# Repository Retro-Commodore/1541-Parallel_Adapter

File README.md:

# RCEU1505 - 1541-Parallel_Adapter
This is an adapter to easier add a parallel port for the Commodore 1541 and 1541-II diskette drive.
You can (and should) read more on Peter's site https://ist.uwaterloo.ca/~schepers/1541par.html

Item list.
* 15CM 10 wire flatcable.
  * or 8 wire flatcable for ZoomFloppy.
* 15pin D-sub female(not the VGA type connector), either solder or for IDC ribbon cable (last one recommended).
* 40 pins IC socket.
* 2 x 20 pins sil header male-male. (turned/tulip recommended).

All items can be found on eBay or your favorite electronics pusher.

**Let the PCB be as thin as possible, otherwise you need thicker washers. Testet is a 0.8mm thick adapter. **

Washers are needed for the 1541-II drive to lift the mechanical parts.
1.6mm (2 x 0.8mm) height with an inner diameter of 4mm is just sufficient to lift the drive.
It hasn't been physically testet on a 1541 drive, if you're intending to use this drive, let me know how it fits, so I can update this document.

Connecting the adapter to ZoomFloppy is described below, if you need to connect the drive to a C64, you should visit Peter's site for more help.

On 1541 shortboard the chip is UC3, and on the long board it's UAB1.

For solder pins

Adapter | 15pin D-sub female
------------ | -------------
Pin 1 | Pin 1
Pin 2 | Pin 2
Pin 3 | Pin 3
Pin 4 | Pin 4
Pin 5 | Pin 5
Pin 6 | Pin 6
Pin 7 | Pin 7
Pin 8 | Pin 8

Soldering the cable for this is just the same pinout

15pin D-sub male | 15pin D-sub female
------------ | -------------
Pin 1 | Pin 1
Pin 2 | Pin 2
Pin 3 | Pin 3
Pin 4 | Pin 4
Pin 5 | Pin 5
Pin 6 | Pin 6
Pin 7 | Pin 7
Pin 8 | Pin 8

If you choose to use the connector to press the IDC connector and don't want to use a 15 pin cable wasting 7 wires, you can hook it up like this.

Adapter | 15pin D-sub female (IDC)
------------ | -------------
Pin 1 | Pin 1
Pin 2 | Pin 9
Pin 3 | Pin 2
Pin 4 | Pin 10
Pin 5 | Pin 3
Pin 6 | Pin 11
Pin 7 | Pin 4
Pin 8 | Pin 12

The cable should be soldered accordingly

15pin D-sub female | 15pin D-sub male
------------ | -------------
Pin 1 | Pin 1
Pin 2 | Pin 9
Pin 3 | Pin 2
Pin 4 | Pin 10
Pin 5 | Pin 3
Pin 6 | Pin 11
Pin 7 | Pin 4
Pin 8 | Pin 12

Many thanks to [Peter Schepers](https://ist.uwaterloo.ca/~schepers/1541par.html).

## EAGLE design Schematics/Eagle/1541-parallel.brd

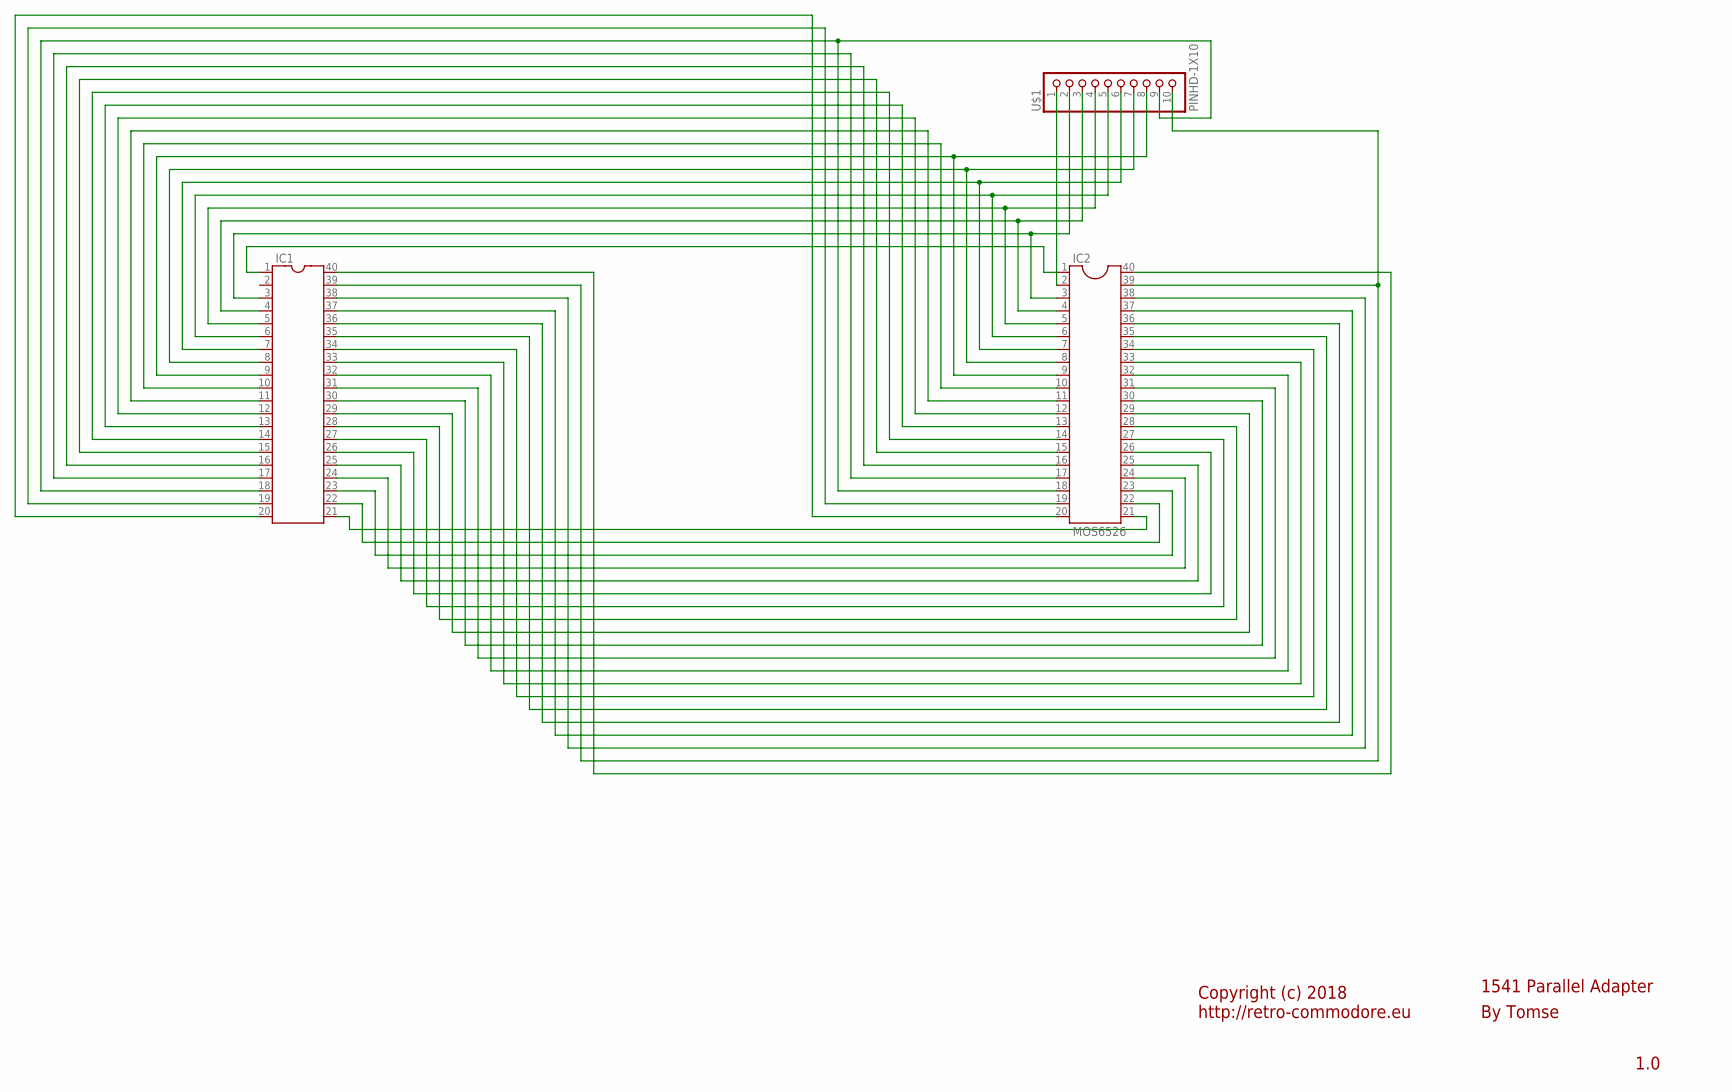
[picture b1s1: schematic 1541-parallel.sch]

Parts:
IC1: IC-PACKAGE_DIL40
IC2: MOS6526; DIL40
U$1: PINHD-1X10; 1X10-BIG

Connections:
unnamed: IC1.1, IC2.1
unnamed: IC1.3, IC2.3, U$1.2
unnamed: IC1.4, IC2.4, U$1.3
unnamed: IC1.5, IC2.5, U$1.4
unnamed: IC1.6, IC2.6, U$1.5
unnamed: IC1.7, IC2.7, U$1.6
unnamed: IC1.8, IC2.8, U$1.7
unnamed: IC1.9, IC2.9, U$1.8
unnamed: IC1.10, IC2.10
unnamed: IC1.11, IC2.11
unnamed: IC1.12, IC2.12
unnamed: IC1.13, IC2.13
unnamed: IC1.14, IC2.14
unnamed: IC1.15, IC2.15
unnamed: IC1.16, IC2.16
unnamed: IC1.17, IC2.17
unnamed: IC1.18, IC2.18, U$1.9
unnamed: IC1.19, IC2.19
unnamed: IC1.20, IC2.20
unnamed: IC1.21, IC2.21
unnamed: IC1.22, IC2.22
unnamed: IC1.23, IC2.23
unnamed: IC1.24, IC2.24
unnamed: IC1.25, IC2.25
unnamed: IC1.26, IC2.26
unnamed: IC1.27, IC2.27
unnamed: IC1.28, IC2.28
unnamed: IC1.29, IC2.29
unnamed: IC1.30, IC2.30
unnamed: IC1.31, IC2.31
unnamed: IC1.32, IC2.32
unnamed: IC1.33, IC2.33
unnamed: IC1.34, IC2.34
unnamed: IC1.35, IC2.35
unnamed: IC1.36, IC2.36
unnamed: IC1.37, IC2.37
unnamed: IC1.38, IC2.38
unnamed: IC1.39, IC2.39, U$1.10
unnamed: IC1.40, IC2.40
unnamed: IC2.2, U$1.1

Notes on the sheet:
1.0
1541 Parallel Adapter
Copyright (c) 2018 http://retro-commodore.eu
By Tomse

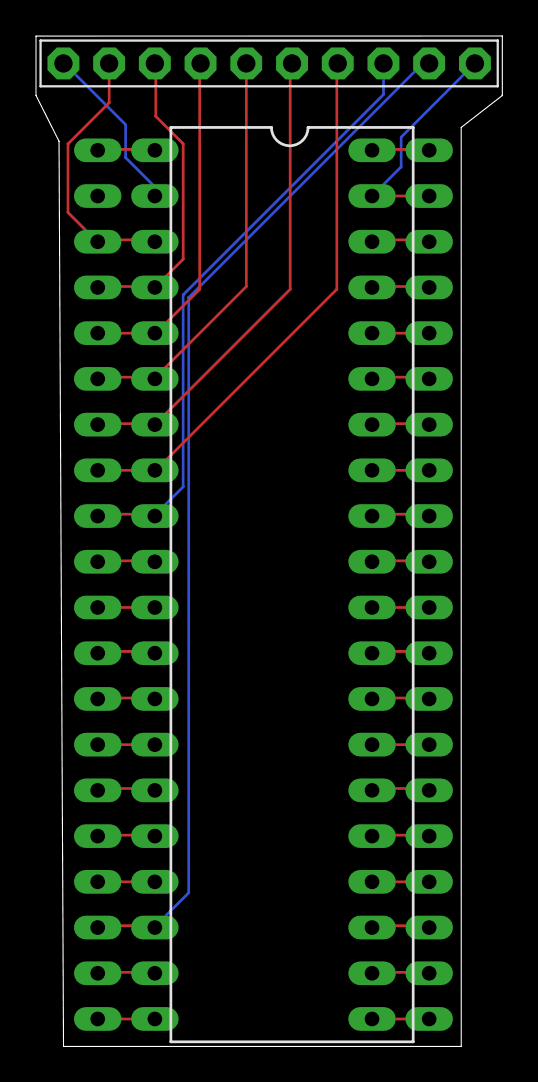
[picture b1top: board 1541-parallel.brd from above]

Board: 2 copper layers, 25.9 x 56.1 mm, 3 parts (0 on the bottom side), 40 nets.

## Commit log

2019-01-18 Initial release
2019-02-06 added pics for documentation
    added pics for documentation
2020-04-06 Fixing dirnaming
2020-04-06 Cosmetic Changes

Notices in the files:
Schematics/Eagle/1541-parallel.brd:
Copyright (c) 2018-2020
